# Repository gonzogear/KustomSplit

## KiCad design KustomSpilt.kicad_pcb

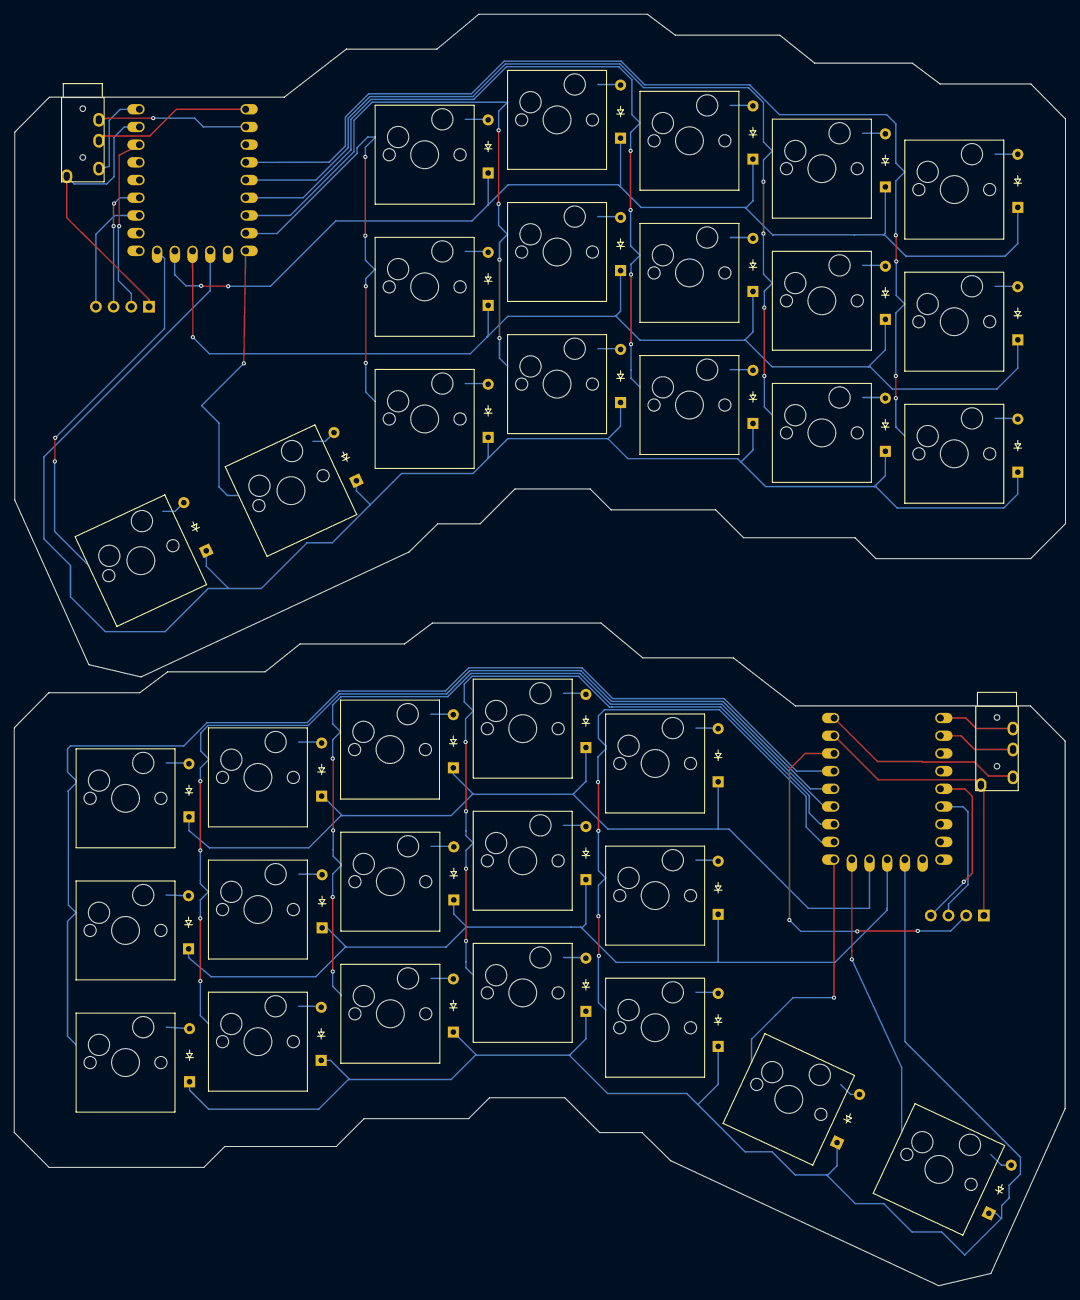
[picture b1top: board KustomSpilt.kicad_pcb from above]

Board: 2 copper layers, 150.9 x 182.5 mm, 74 parts (0 on the bottom side), 68 nets.

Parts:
D1, D2, D3, D4, D5, D6, D7, D8, D9, D10, D11, D12, D13, D14, D15, D16, D17, D18, D19, D20, D21, D22, D23, D24, D25, D26, D27, D28, D29, D30, D31, D32, D33, D34: Diode; Diode_DO-35
J1, J2.1: OLED_128x32
S1, S2, S3, S4, S5, S6, S7, S8, S9, S10, S11, S12, S13, S14, S15, S16, S17, S18, S19, S20, S21, S22, S23, S24, S25, S26, S27, S28, S29, S30, S31, S32, S33, S34: Keyswitch; Hotswap_MX
U1, U3: RP2040_Zero
U2, U4: TRRS; TRRS_PJ-320A

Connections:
3.3v: J1.2 (VCC), U1.21 (3V3)
3.3v1: J2.1.2 (VCC), U3.21 (3V3)
5v: U1.23 (5V), U2.2 (TIP)
5v1: U3.23 (5V), U4.2 (TIP)
Col0: S1.1, S2.1, S3.1, U1.4 (3)
Col1: S4.1, S5.1, S6.1, U1.5 (4)
Col2: S7.1, S8.1, S9.1, U1.6 (5)
Col3: S10.1, S11.1, S12.1, U1.7 (6)
Col4: S13.1, S14.1, S15.1, U1.8 (7)
Col5: S16.1, U1.9 (8)
Col6: S17.1, U1.14 (13)
Col8: S18.1, S23.1, S28.1, U3.20 (29)
Col9: S19.1, S24.1, S29.1, U3.19 (28)
Col10: S20.1, S25.1, S30.1, U3.18 (27)
Col11: S21.1, S26.1, S31.1, U3.17 (26)
Col12: S22.1, S27.1, S32.1, U3.16 (15)
Col13: S33.1, U3.15 (14)
Col14: S34.1, U3.14 (13)
Gnd: J1.1 (GND), U1.22 (GND), U2.1 (SLEEVE)
Gnd1: J2.1.1 (GND), U3.22 (GND), U4.1 (SLEEVE)
unnamed: D1.2 (A), S1.2
unnamed: D2.2 (A), S2.2
unnamed: D3.2 (A), S3.2
unnamed: D4.2 (A), S4.2
unnamed: D5.2 (A), S5.2
unnamed: D6.2 (A), S6.2
unnamed: D7.2 (A), S7.2
unnamed: D8.2 (A), S8.2
unnamed: D9.2 (A), S9.2
unnamed: D10.2 (A), S10.2
unnamed: D11.2 (A), S11.2
unnamed: D12.2 (A), S12.2
unnamed: D13.2 (A), S13.2
unnamed: D14.2 (A), S14.2
unnamed: D15.2 (A), S15.2
unnamed: D16.2 (A), S16.2
unnamed: D17.2 (A), S17.2
unnamed: D18.2 (A), S18.2
unnamed: D19.2 (A), S19.2
unnamed: D20.2 (A), S20.2
unnamed: D21.2 (A), S21.2
unnamed: D22.2 (A), S22.2
unnamed: D23.2 (A), S23.2
unnamed: D24.2 (A), S24.2
unnamed: D25.2 (A), S25.2
unnamed: D26.2 (A), S26.2
unnamed: D27.2 (A), S27.2
unnamed: D28.2 (A), S28.2
unnamed: D29.2 (A), S29.2
unnamed: D30.2 (A), S30.2
unnamed: D31.2 (A), S31.2
unnamed: D32.2 (A), S32.2
unnamed: D33.2 (A), S33.2
unnamed: D34.2 (A), S34.2
RX: U1.2 (1), U2.4 (RING2)
RX1.: U3.1 (0), U4.4 (RING2)
Row0: D1.1 (K), D4.1 (K), D7.1 (K), D10.1 (K), D13.1 (K), U1.13 (12)
Row1: D2.1 (K), D5.1 (K), D8.1 (K), D11.1 (K), D14.1 (K), U1.12 (11)
Row2: D3.1 (K), D6.1 (K), D9.1 (K), D12.1 (K), D15.1 (K), D16.1 (K), D17.1 (K), U1.11 (10)
Row4: D18.1 (K), D19.1 (K), D20.1 (K), D21.1 (K), D22.1 (K), U3.13 (12)
Row5: D23.1 (K), D24.1 (K), D25.1 (K), D26.1 (K), D27.1 (K), U3.12 (11)
Row6: D28.1 (K), D29.1 (K), D30.1 (K), D31.1 (K), D32.1 (K), D33.1 (K), D34.1 (K), U3.11 (10)
SCL: J1.3 (SCL), U1.18 (27)
SCL1: J2.1.3 (SCL), U3.6 (5)
SDA: J1.4 (SDA), U1.17 (26)
SDA1: J2.1.4 (SDA), U3.5 (4)
TX: U1.1 (0), U2.3 (RING1)
TX11: U3.2 (1), U4.3 (RING1)
